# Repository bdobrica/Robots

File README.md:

# Robots
 Or at least my understanding of robots: electronics mixed with software =)

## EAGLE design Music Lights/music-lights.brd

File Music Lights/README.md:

# Music Lights #

This is a project that controls a WS2812B led strip using an ESP8266 using data from a sound snesor. A more detailed explanation is available here (in Romanian, for now): [link](https://ublo.ro/muzica-si-lumina/).

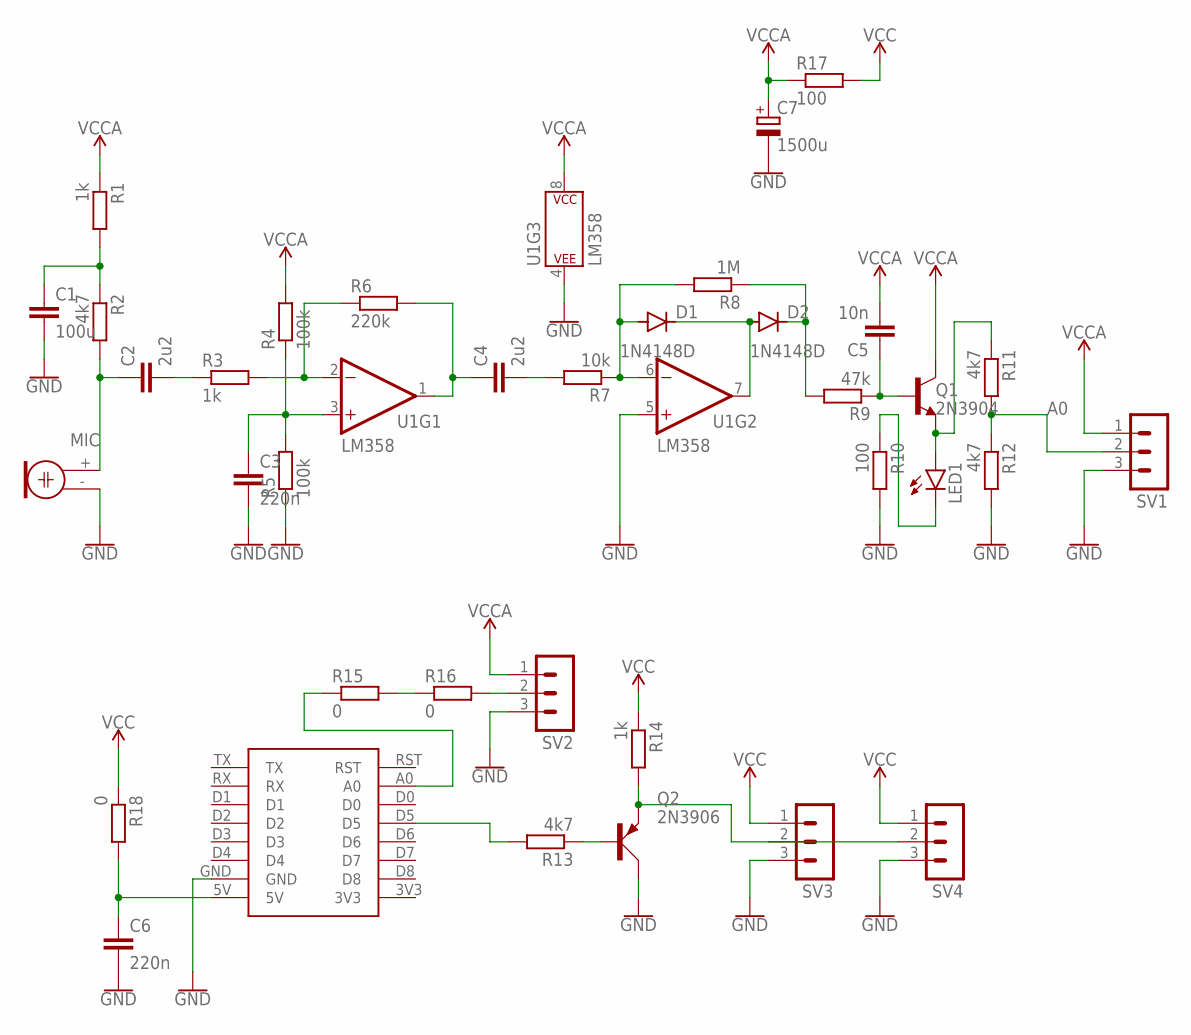
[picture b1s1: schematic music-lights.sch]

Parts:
C1: 100u; C050-024X044
C2, C4: 2u2; C050-024X044
C3, C6: 220n; C050-024X044
C5: 10n; C050-024X044
C7: 1500u; TT5D7L
D1, D2: 1N4148D; DO35-7
LED1: LED5MM
MIC: ELECTRET; 9.7ELECTRET
Q1: 2N3904; TO92
Q2: 2N3906; TO92D
R1, R3, R14: 1k; 0207/7
R2, R11, R12, R13: 4k7; 0207/7
R4, R5: 100k; 0207/7
R6: 220k; 0207/7
R7: 10k; 0207/7
R8: 1M; 0207/7
R9: 47k; 0207/7
R10, R17: 100; 0207/7
R15, R16, R18: 0; 0207/7
SV1, SV2, SV3, SV4: MA03-1
U1: LM358; DIP08-KIT
U$1: 8266MINI

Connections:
A0: R11.2, R12.1, SV1.2
GND: C1.2, C3.2, C6.2, C7.-, MIC.- (1), Q2.C, R5.1, R10.2, R12.2, SV1.3, SV2.3, SV3.3, SV4.3, U1.4 (P$V-), U1.5 (+IN), U$1.GND
unnamed: R13.2, U$1.D5
unnamed: Q2.B, R13.1
unnamed: C2.1, MIC.+ (2), R2.2
unnamed: C1.1, R1.2, R2.1
unnamed: C2.2, R3.1
unnamed: C3.1, R4.1, R5.2, U1.3 (+IN)
unnamed: R3.2, R6.1, U1.2 (-IN)
unnamed: C4.1, R6.2, U1.1 (OUT)
unnamed: C4.2, R7.2
unnamed: D1.C, D2.A, U1.7 (OUT)
unnamed: D1.A, R7.1, R8.2, U1.6 (-IN)
unnamed: D2.C, R8.1, R9.2
unnamed: C5.1, Q1.2 (B), R9.1
unnamed: LED1.K (C), R10.1
unnamed: LED1.A, Q1.3 (E), R11.1
unnamed: Q2.E, R14.2, SV3.2, SV4.2
unnamed: R16.2, SV2.2
unnamed: R15.1, U$1.A0
unnamed: R15.2, R16.1
unnamed: C6.1, R18.2, U$1.5V
VCC: R14.1, R17.2, R18.1, SV3.1, SV4.1
VCCA: C5.2, C7.+, Q1.1 (C), R1.1, R4.2, R17.1, SV1.1, SV2.1, U1.8 (P$V+)

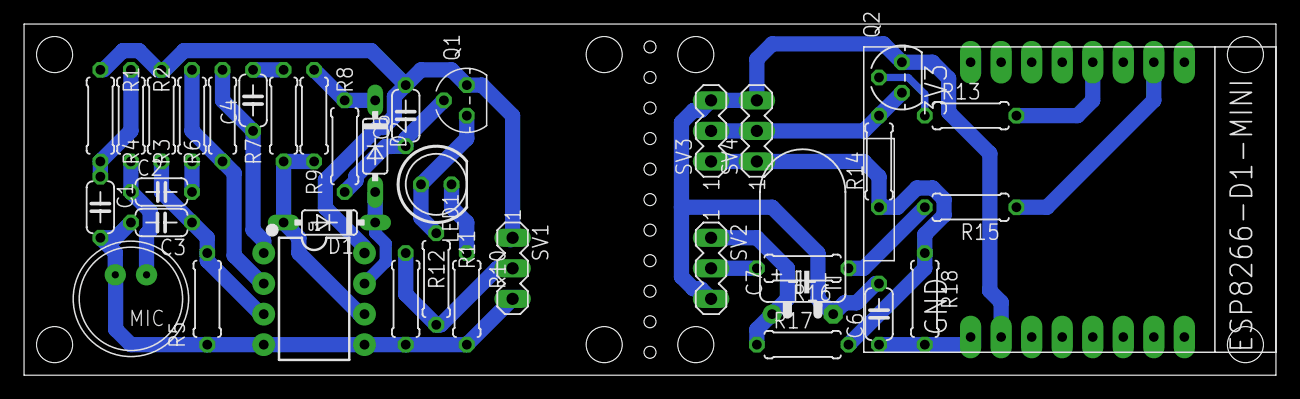
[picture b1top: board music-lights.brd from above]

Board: 2 copper layers, 104.1 x 29.2 mm, 37 parts (0 on the bottom side), 24 nets.

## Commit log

2021-01-03 Create music-lights.ino
    - the Arduino sketch for the ESP8266 module;
    - the settings can be updated via WiFi;
    - also, the settings are saved in the ESP8266 EEPROM;
    - (this version wasn't tested);
2021-01-03 Create music-lights.brd
    - the music lights board (improved version that contains a filtering RC filter for the audio sensor);
2021-01-03 Create music-lights.sch
    - the music lights schematics (improved version that contains a filtering RC filter for the audio sensor);
    - also, it has a header for WS2812B led strip;
2021-01-03 Create README.md
    - short readme;

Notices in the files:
parts and their libraries:
SparkFun-IC-Amplifiers: Licensing: Creative Commons ShareAlike 4.0 International - https://creativecommons.org/licenses/by-sa/4.0
